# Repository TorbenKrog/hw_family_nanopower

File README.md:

# family_nanopower
Hardware repository for the nanopower family like the P60/P80, BPX and BP8

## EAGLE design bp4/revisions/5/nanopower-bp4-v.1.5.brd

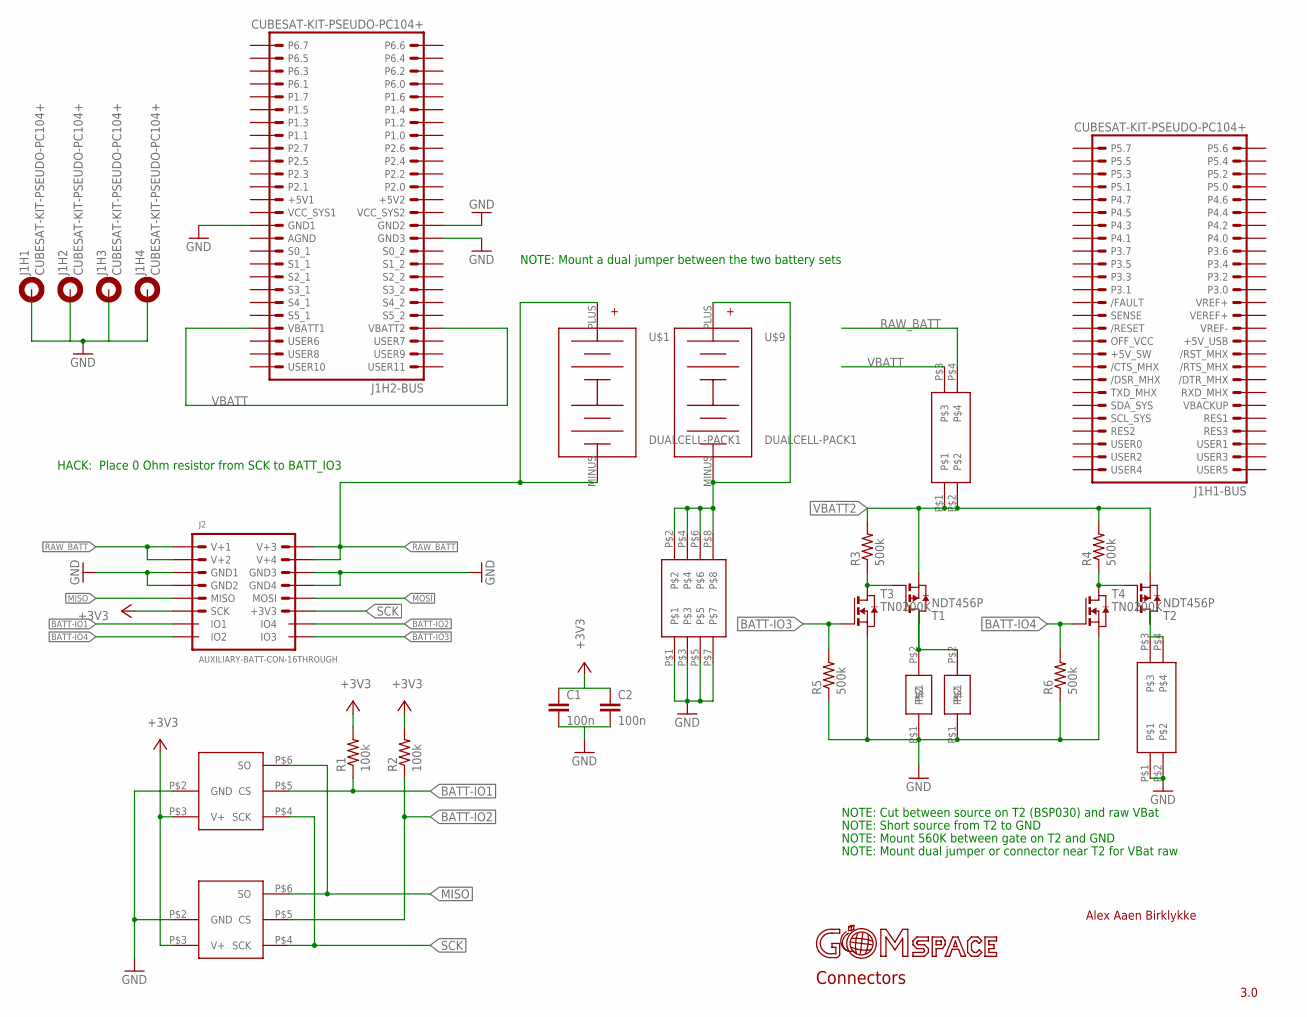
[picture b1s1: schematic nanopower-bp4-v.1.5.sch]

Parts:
C1, C2: 100n; C0603
J1: CUBESAT-KIT-PSEUDO-PC104+; CUBESAT-KIT
J2: AUXILIARY-BATT-CON-16THROUGH; 2X8HEADER
R1, R2: 100k; R0603
R3, R4, R5, R6: 500k; R0603
T1, T2: NDT456P; SOT223
T3, T4: TN0200K; SOT-23
U$1, U$9: DUALCELL-PACK1; P30U-BATT-PACK
U$2, U$3: TMP121; SSOT-6
U$4, U$5: HEATER
U$6, U$10: 2X2MM
U$7: 4X2MM

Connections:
+3V3: C1.1, C2.1, J2.P$6 (SCK), R1.2, R2.2, U$2.P$3 (V+), U$3.P$3 (V+)
BATT-IO1: J2.P$7 (IO1), R1.1, U$2.P$5 (CS)
BATT-IO2: J2.P$10 (IO4), R2.1, U$3.P$5 (CS)
BATT-IO3: J2.P$9 (IO3), R5.2, T3.3 (G)
BATT-IO4: J2.P$8 (IO2), R6.2, T4.3 (G)
GND: C1.2, C2.2, J1.H2-$29 (GND1), J1.H2-$30 (GND2), J1.H2-$32 (GND3), J1.HOLE$1 (MOUNT), J1.HOLE$2 (MOUNT), J1.HOLE$3 (MOUNT), J1.HOLE$4 (MOUNT), J2.P$3 (GND1), J2.P$4 (GND2), J2.P$13 (GND4), J2.P$14 (GND3), R5.1, R6.1, T3.2 (S), T4.2 (S), U$2.P$2 (GND), U$3.P$2 (GND), U$4.P$1, U$5.P$1, U$6.P$1, U$6.P$2, U$7.P$1, U$7.P$3, U$7.P$5, U$7.P$7
MISO: J2.P$5 (MISO), U$2.P$6 (SO), U$3.P$6 (SO)
MOSI: J2.P$12 (MOSI)
unnamed: U$7.P$2, U$7.P$4, U$7.P$6, U$7.P$8, U$9.MINUS, U$9.PLUS
unnamed: T2.2 (D), T2.4 (D2), U$6.P$3, U$6.P$4
unnamed: T1.2 (D), T1.4 (D2), U$4.P$2, U$5.P$2
NT3: R3.1, T1.1 (G), T3.1 (D)
NT4: R4.1, T2.1 (G), T4.1 (D)
RAW_BATT: J2.P$1 (V+1), J2.P$2 (V+2), J2.P$15 (V+4), J2.P$16 (V+3), U$1.MINUS, U$1.PLUS, U$10.P$4
SCK: J2.P$11 (+3V3), U$2.P$4 (SCK), U$3.P$4 (SCK)
VBATT: J1.H2-$45 (VBATT1), J1.H2-$46 (VBATT2), U$10.P$3
VBATT2: R3.2, R4.2, T1.3 (S), T2.3 (S), U$10.P$1, U$10.P$2

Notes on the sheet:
Connectors
HACK: Place 0 Ohm resistor from SCK to BATT_IO3
NOTE: Cut between source on T2 (BSP030) and raw VBat
NOTE: Short source from T2 to GND
NOTE: Mount 560K between gate on T2 and GND
NOTE: Mount dual jumper or connector near T2 for VBat raw
NOTE: Mount a dual jumper between the two battery sets

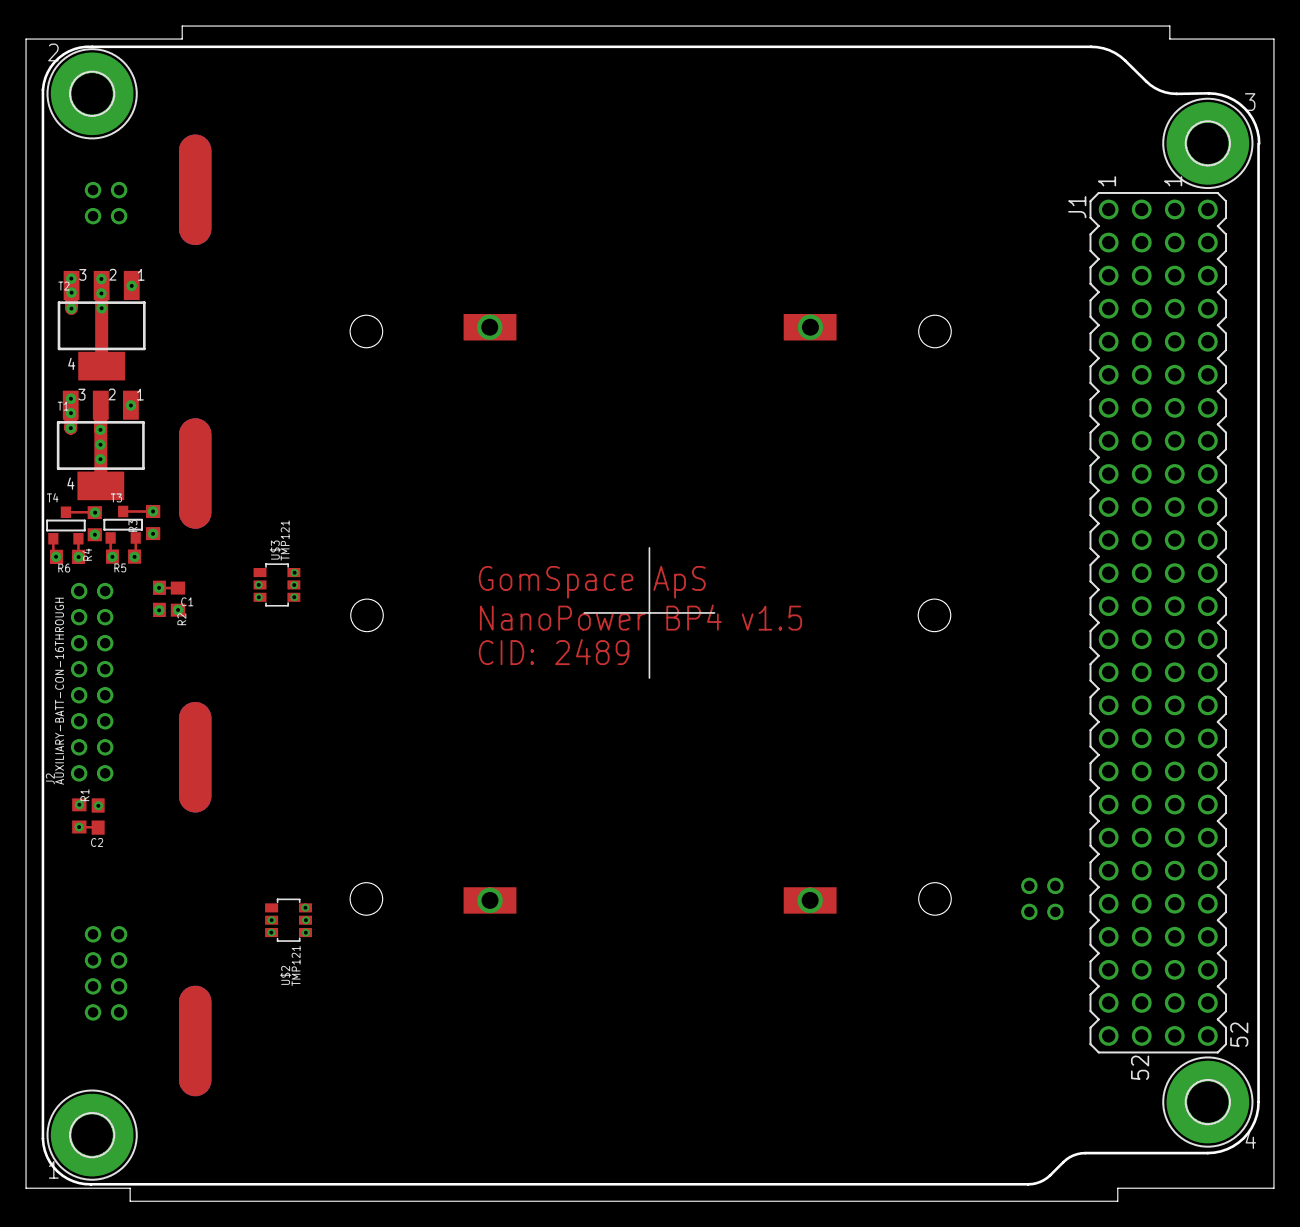
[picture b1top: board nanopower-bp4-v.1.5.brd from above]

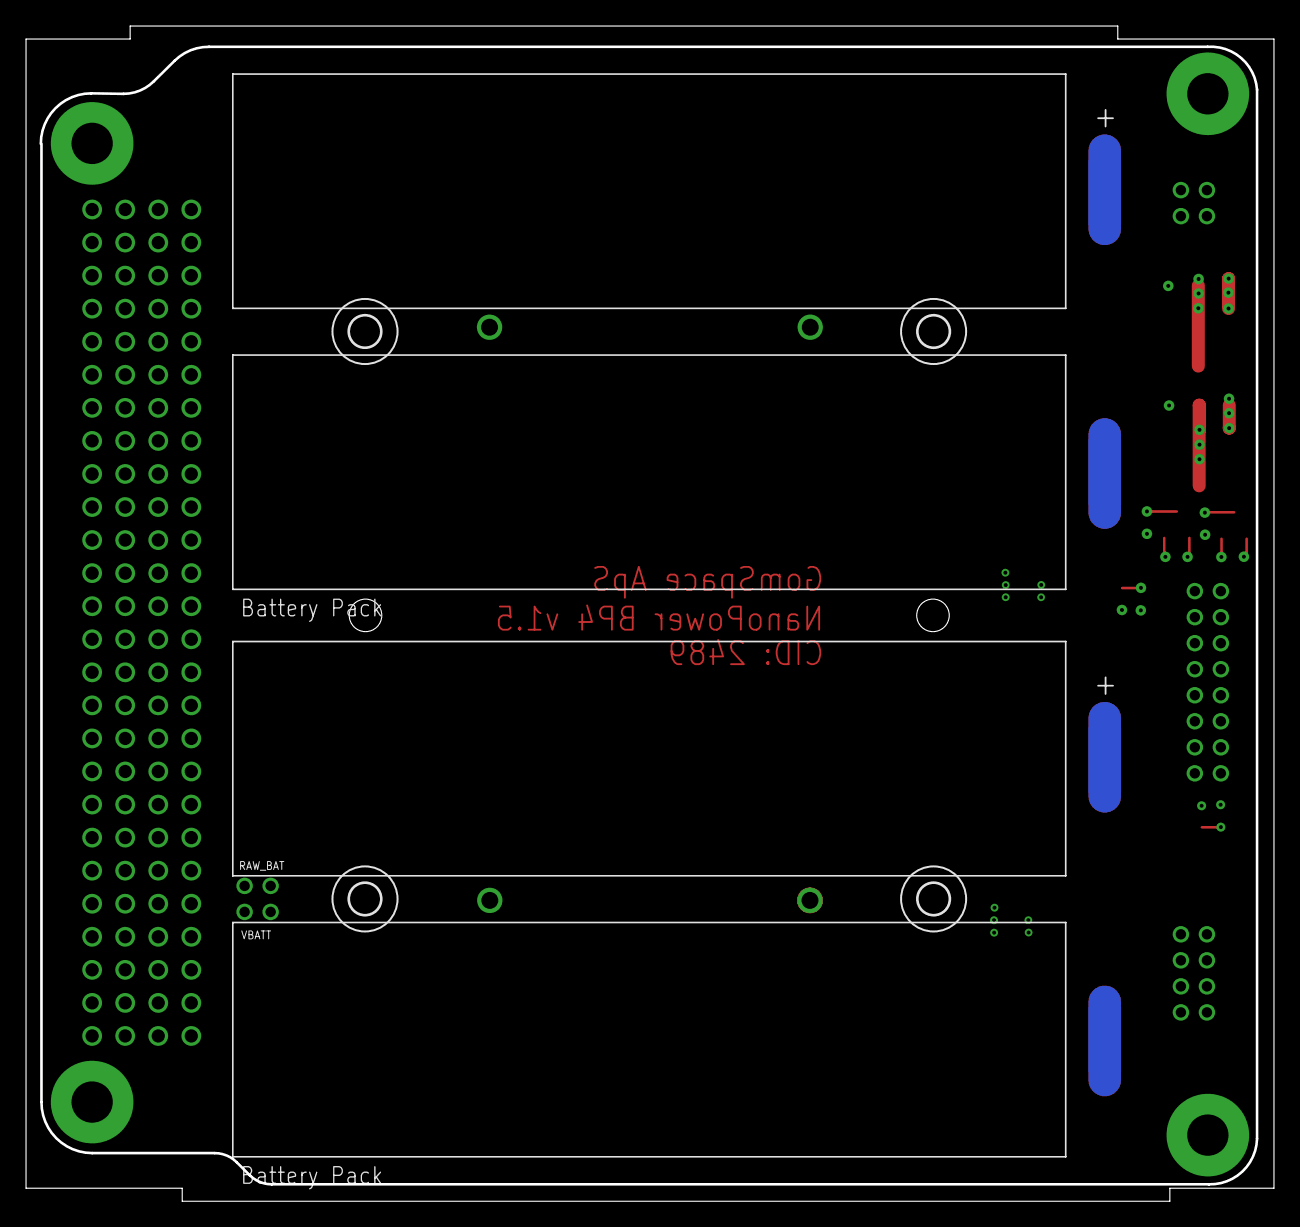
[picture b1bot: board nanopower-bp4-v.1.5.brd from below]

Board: 6 copper layers, 95.9 x 90.3 mm, 23 parts (2 on the bottom side), 16 nets.

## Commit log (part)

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2018-05-02 Updated Killswitch circuitry
    Changes affect PMU and ACU
2018-05-02 Minor update
    specified components values
2018-05-03 p80 acu: stuff
2018-05-04 added point
2018-05-07 added to pmu changelog
2018-05-08 PDU update
2018-05-14 WP31 TSP-8UL harness
    Initial harness drawing
2018-05-15 added
2018-05-15 tsp-8ul-panel v2
2018-05-15 Updated sch
2018-05-16 Adding TSP-8UL Harness
    Working copy
2018-05-16 Working copy
2018-05-16 p80 added killswitch overview v2 again
2018-05-16 ffc breakout added pcb spec
2018-05-16 pmu changelog rescue
2018-05-16 Schematic updated with new driver for high voltege switch
2018-05-17 p80 acu: updated loadswitch, watchdog and vboost reference
2018-05-18 TSP-8UL hatch
2018-05-18 TSP-8UL_Panel_2
2018-05-18 fixed acu changelog after git fuckup
2018-05-18 changelog: commented on changing LDO to SMPS
2018-05-22 acu: changed vbat switch to comply with 'new' ks design
2018-05-22 acu changelog edit
2018-05-22 pmu stuff
2018-05-23 Schematic update
2018-05-23 pmu: MCU changed to 100 pin version
2018-05-23 pmu changelog
2018-05-24 fixed mess
2018-05-24 pmu: reversed deployment connectors
2018-05-24 Schematic updated
2018-05-24 designator update
2018-05-28 Merge changes
    Add changes lost in disrupted commit history
    Add updates to Killswitch changes
2018-05-28 Change OR'ing for LDO input
2018-05-28 Update information regarding LTC3936
2018-05-28 Add killswitch simulation
2018-05-28 Optimize simulation for LTC3639
    Lower coil inductance
    Lower output capacitance
    Increased efficiency
2018-05-29 pmu: more changes implemented
2018-05-29 Add v3 of KS
    Simplified to two types of circuit
    Theoretical endless nodes on KS bus
    KS active must be a short
2018-05-29 Sch. update
2018-05-30 pmu: changes
2018-05-30 pmu: added PPS receiver
2018-05-30 pmu: moved PPS to external interrupt input on MCU
2018-05-31 schmatic update
2018-05-31 Special HV page updated
2018-05-31 TVS diode added on debug
2018-06-01 Harness drawings Preliminary
    Harness drawings Preliminary
2018-06-01 pmu: updated deployment power channels
2018-06-01 p80 acu: added grounding scheme to changelog
2018-06-04 design updated
2018-06-04 output circuit updated
2018-06-06 p80 acu stuff
2018-06-06 pmu: ready for sch review
2018-06-06 pmu: stuff
2018-06-06 Variant updated
2018-06-07 p80 acu: changed fram
2018-06-07 Attempt for cleanup
2018-06-11 pmu: review stuff
2018-06-11 Smal update in project files
2018-06-13 pmu: added logic for overriding vcc wd
2018-06-14 possible to program pmu first time
2018-06-15 pmu: ready for rereview
2018-06-18 Update KS circuitry
2018-06-18 Add TVS diode to GOSH2
2018-06-18 Update according to change log
    Remove SSFM circuitry
    Remove Vbat net
    Remove I2C net label, wire directly to port
    Remove VsunN net, wire directly to port
2018-06-18 pmu: added 10R to FPP GND
2018-06-18 pmu added NM comment
2018-06-18 pmu added comments
2018-06-18 Components placed on PCB. I2C name changed on MAIN
2018-06-19 Update capacitors
    Change input capacitors to 2x2,2µF
    Change output capacitors to 3x4,7µF
    Change OR'ing diodes to CDBU0245
2018-06-19 Updated according to change log
    Change inductor to WE-PDF 22µH
    Revert input capacitor to 1µF
    Add input capacitor
    Add output capacitors
2018-06-19 Merged in changes to project
    Backup stored in *_old files
2018-06-19 Update to reflect changes
2018-06-20 Working copy
    Working copy
2018-06-20 Update components
    Update components from vaults rather than just changing its values
2018-06-20 Update according to JOKR report
    Add 330ohm series resistor
    Change voltage dividers from Vboost and Vsun
2018-06-21 Change netlabel nRESET to nMR to match rest of sheet
2018-06-21 Annotation
2018-06-21 Fixing compiler errors
2018-06-22 pmu: sent to layouter
2018-06-22 VBAT and V_BAT merged
2018-06-22 Net name changed in single-buck
2018-06-25 Net name changed VBAT to V_BAT
2018-06-26 Push to BGS for mech outline
2018-06-26 p80 scu: added to changelog
2018-06-26 p80 acu: added mechanical drawings to pcb
2018-06-26 working copy
    Updated setup of MCU
2018-06-27 pmu: bom ready
2018-06-27 pmu: throughole variant
2018-06-27 pmu: variants ready for IFS
2018-06-28 Component value changes made
    Pilot series PCBA was tested and components were changed, primarily at the SC circuits and KS-circuit.
2018-06-29 acu: stuff
2018-06-29 small updated
2018-06-29 Added a test-point to the layout
    For accomodating test of fuse...
2018-06-29 pmu: sent for routing
2018-06-29 Commit for Mech review
2018-07-02 added TP to BP8
    for testing fuse
2018-07-02 Global annotation
2018-07-03 p80 acu: BOM only missing load switch
2018-07-03 Optimization
    99.41% Completed
    - 6 components missing - redundant?
    - Via stiching missing
    Routing optimization to improve ground pours
2018-07-03 Working copy
    Update
2018-07-03 Remove redundant bypass caps
2018-07-03 In progress updates after review
    Change location of TVS diode, capacitors and resistors for input on boost converters
2018-07-04 p80 acu: input generated for IFS, fixed designators for 910k resistors
2018-07-05 Components value changed on Low voltage load-switch
2018-07-05 Completed after review
    Change vias annular inner layers to 0.4mm
    Add thermal via to gate driver
    Change layout of inputs from PV source
    Add fill to grouped vias
    Add 0.6mm trace between leads in gecko conn
    Remove net antenna
2018-07-05 Variants
2018-07-06 BP8 updated for ECO
    Compiled P&P and Sch for IFS after ECO approval
2018-07-06 Add GND via stiching
2018-07-06 Variants update
2018-07-09 pmu: layout return for review
2018-07-09 TSP panel rev3 started
2018-07-11 p80 acu: inner polygon clearance changed to 0.2 mm
2018-07-11 TSP-8UL-Release PCB R 2
2018-07-11 TSP-8UL-Panel R3 updates
2018-07-13 OSIRIS stack changes
2018-07-16 pmu added variant for schematic export
2018-07-16 p80 acu and pmu: ready IFS documents export
2018-07-25 Alpha release
    Move Detector PCB 0.3mm inwards
    Change J8 to Gecko type
    Move J7 to be aligned with clamp
    Move affected/violating components
    Routing affected/violating traces
    Readd teardrops
2018-08-06 Reduced width on castelatted vias
2018-08-06 Minor fix
2018-08-07 Alpha release 2
    Change boardshape
    Add ground vias
    Readd teardrops
    Repour all polygons
    DRC errors: 0
2018-08-10 Documentation
2018-08-22 small edit of layout
    closed paste mask on battery tabs and made a minor correction on a track in signal layer 1 around the fuse. No functional changes.
2018-08-22 Page number update
2018-08-23 p60-dock: added PEM nuts and Stackconnector to CP
2018-08-23 Updated Schematic to Vault
2018-08-23 Sync Sch and PCB with new Vault comp
2018-08-24 Correction of inne layer around batt tabs
    Copper pour was covering the batt tab holes in the gerber files. This is now corrected...
2018-08-27 Connector NM change
2018-08-28 Harness Rev 4
2018-08-28 Working copy for Next revision of TSP-8UL harness
2018-08-30 updated pcb stackup and silkscreen top
2018-08-31 Harness working copy
    Almost ready to send to Amgab - awaiting Amgab issues and comments + IFS numbers on new wires
2018-09-06 TSP-8UL-Paddle updated
2018-09-06 TSP-8UL-Paddele update
2018-09-06 GSSB and Paddle PCB updates
2018-09-14 Paddle PCB
2018-09-18 BP4 update
    Updated the BP4 schematics - prettified and added some comments.
2018-09-25 BP4 cleanup
2018-10-04 Update in TSP-8UL-Paddle Gerbers
2018-10-04 harness
2018-10-09 IFS version 1
2018-10-09 Small update
2018-10-09 Changed the PCB version back to CID: 4606
2018-10-10 Base line for IFS Eng. Rev. 2.0
2018-10-10 p60 hr tester details
2018-10-15 harness bp4
2018-10-25 p60 pdu: added outjob and modified cp for IFS implementation
2018-10-25 Update nanopower/P60/rev3/P60-PDU/Gomspace_vault5.OutJob
    bgs
2018-10-25 Start of P80-PDU400 rev. 3
2018-11-09 Updated Kapton for Anode/Cathode Cells
2018-11-21 BPX with vault components
2018-12-10 pmu: updated change log
2019-01-17 p80 pmu: added to changelog
2019-01-25 DualCell Kapton for PV-side updated
2019-03-01 harness updates
2019-03-13 p60-acu: cosmetic pcb stuff
2019-04-01 pmu: added to changelog
2019-07-12 Newest
2019-07-15 added fabrication outputs for P60 dock rev5
2019-07-15 added p60 checkout DB
2019-07-19 updated changelog
2019-07-19 First S2C
2019-09-02 New PCB
    New
2019-09-23 renamed pmu project to pmu-2
2019-09-23 added gitignore
2019-09-23 git from altium test
2019-10-31 changed default view on P80 PDU pcb
2019-11-21 corrected cathode markings on P80 ACU TVS diodes
2020-02-13 Long flex PCB and same reverse Ready for review.
2020-02-18 Update P80_ACU_Hardware_Change_Log.docx
    Updated with findings on PCB rev 2
2020-02-18 New version dual cell
    Updates on connectors...
2020-02-19 Added documentation file.
2020-02-19 added layer stack legend
2020-02-19 Added documentation page to project.
    :-)
2020-02-20 Update Dual_Flex_V2.PrjPcb
    Top and buttom layer aligned.
2020-02-20 Review feedback SKHO
    Review feedback SKHO
2020-02-24 Data til Pridana
    Data til Pridana
2020-02-24 Updates
    :-)
2020-02-24 Kame
2020-02-25 P2C V3 ready for review
    P2C V3 ready for review
2020-02-25 For Review
    For Review
2020-02-26 Design change
    Changed from 2 layer to 4 layer and added connector
2020-02-26 PCB size changed
    PCB size changed; reduced by 4.0mm (x direction) changed mounting holes.
2020-02-26 After review
    After review ( fingers to Flex)
2020-02-26 Updates
    PCB reduced by 4mm :-)
2020-02-27 SKHO
2020-02-27 New design
    Varsion 2 first version.
2020-02-27 Updated :-)
2020-02-28 Update after review
    Please see review report for detailes.
2020-03-02 After review
2020-03-02 Updated
    Changed connector to new type.
2020-03-02 Update
    Added fidusial marks.
2020-03-03 New IFS number to PCB
2020-03-03 Ready for Predana
2020-03-03 minor changes
    Adeded gerber data
2020-03-04 Updated
    Added fiducials
2020-03-04 Update and pached data for manufacturing
2020-03-04 Update and packed data for manufacturing
2020-03-04 Update packed for manufacturing.
2020-03-19 updating BP8 changelog for Rev4, to include additional power saving for VBAT_SENS signal
2020-03-20 Updating change log for Rev 4, suggestion to reduce power consumption by connecting the uC VBAT_SENS to VBAT_KS instead of VBAT_FUSED
2020-03-23 Mindre rettelser ifh til PCB leverandør bemærkninger
2020-03-23 Lavet mindre rettelser i bestilling ifh til leverandør ønsker
2020-03-23 corrections by request from PCB supplier
2020-03-23 Update PCB supplier demand.
2020-03-23 Updates
    PCB supplier requirements.
2020-03-24 added pmu rev3
2020-03-24 Update P80_PDU_Hardware_Change_Log.docx
    Updated
2020-03-24 updated
    Update to revision 3
2020-03-25 New version
    This version has "windows" for connections soldering.
2020-03-25 Updated rev 3
2020-03-26 design update rev 3
    Design update rev 3
2020-03-26 updates on rev 3
2020-03-30 Added diode
2020-03-30 updated
    updated component out of date revision
2020-03-31 Updated rev 3
    updated all out of date components
2020-03-31 performed design update
2020-04-01 updated change log
2020-04-02 Update pmu.PcbDoc
    Updated PCB rooms
2020-04-02 Created new revision 3
    Going to add WDI trigger circuit
2020-04-03 minor updates
2020-04-16 Updated to rev 3
2020-04-21 New TSP
2020-04-23 first
2020-04-28 review
2020-04-28 HW change log updated with Over Current and Over Voltage findings
2020-04-28 remove file from wrong location
2020-04-29 REady to send
2020-04-30 test
2020-05-06 With new header
2020-05-07 Implemented variations
2020-05-11 Updated.
2020-05-12 Update after review
2020-05-12 Update Dual-Cell_V2.SchDoc
    Added stock number on Solar cell.
2020-05-12 Update Dual-Cell_V2.SchDoc
    Changed used PCB number.
2020-05-13 PCB number updated.
2020-05-13 Normal daily work.
2020-05-13 Update Dual-Cell_V2.SchDoc
    PCB number updated
